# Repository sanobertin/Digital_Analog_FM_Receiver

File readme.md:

> [!CAUTION]
> This project is still in progress thus this repo will be changing often. 

## Project Description: 
_This project aims to design and implement a digital FM receiver capable of receiving analog FM radio signals and converting them into digital data. The project will include:_

### Hardware:

**Schematic and PCB Design:** A carefully designed schematic and PCB will be created to ensure optimal performance and reliability of the FM receiver circuit. </br>
**Arduino R4 Microcontroller**: This powerful 32-bit microcontroller will be used to process the digital output and interface with the PC. </br>
**Antenna:** An efficient antenna will be designed to capture FM signals effectively. </br>

### Software:
**Firmware:** The Arduino R4 will be programmed to:
- Receive FM signals from the antenna </br>
- Demodulate the signals to extract audio data </br>
- Convert the audio data into digital format </br>
- Transmit the digital data to the PC via a serial communication protocol </br>
- **PC Application:**
  - C++: Program the arduino microcontroller </br>
  - C#: A C# application will be created to provide a user-friendly interface for controlling the receiver and visualizing the received data. </br> 

**Key Features:**
- **High-Quality Audio Reception:** The receiver will be optimized for clear and accurate audio reproduction. </br>
- **Reliable Data Transmission:** The serial communication between the Arduino and PC will ensure robust data transfer. </br>
- **Flexible Software Interface:** The C++ and C# applications will offer versatility for different use cases. </br>
- **Customizable Hardware:** The modular design will allow for easy customization and experimentation. </br>

## Project Goals:
- Successfully design and build a functional FM receiver. </br>
- Demonstrate the ability to interface the receiver with a PC using a microcontroller. </br>
- Develop user-friendly software applications for data processing and visualization. </br>
- Explore potential applications for the receiver, such as audio streaming, signal analysis, and more. </br>
- By combining hardware and software expertise, this project aims to provide a comprehensive solution for digital FM reception and processing. </br>

## Tools used: 
- KiCAD </br>
- IDEs: </br>
- Google Gemini & GPT 4.xx </br>
- etc. </br>
## Resources: 
- FM Radio block diagrams: https://users.encs.concordia.ca/~paknys/block.pdf
- Antenna selection: https://www.ahsystems.com/articles/antenna-selection.php

### Board Schematic 

### PCB

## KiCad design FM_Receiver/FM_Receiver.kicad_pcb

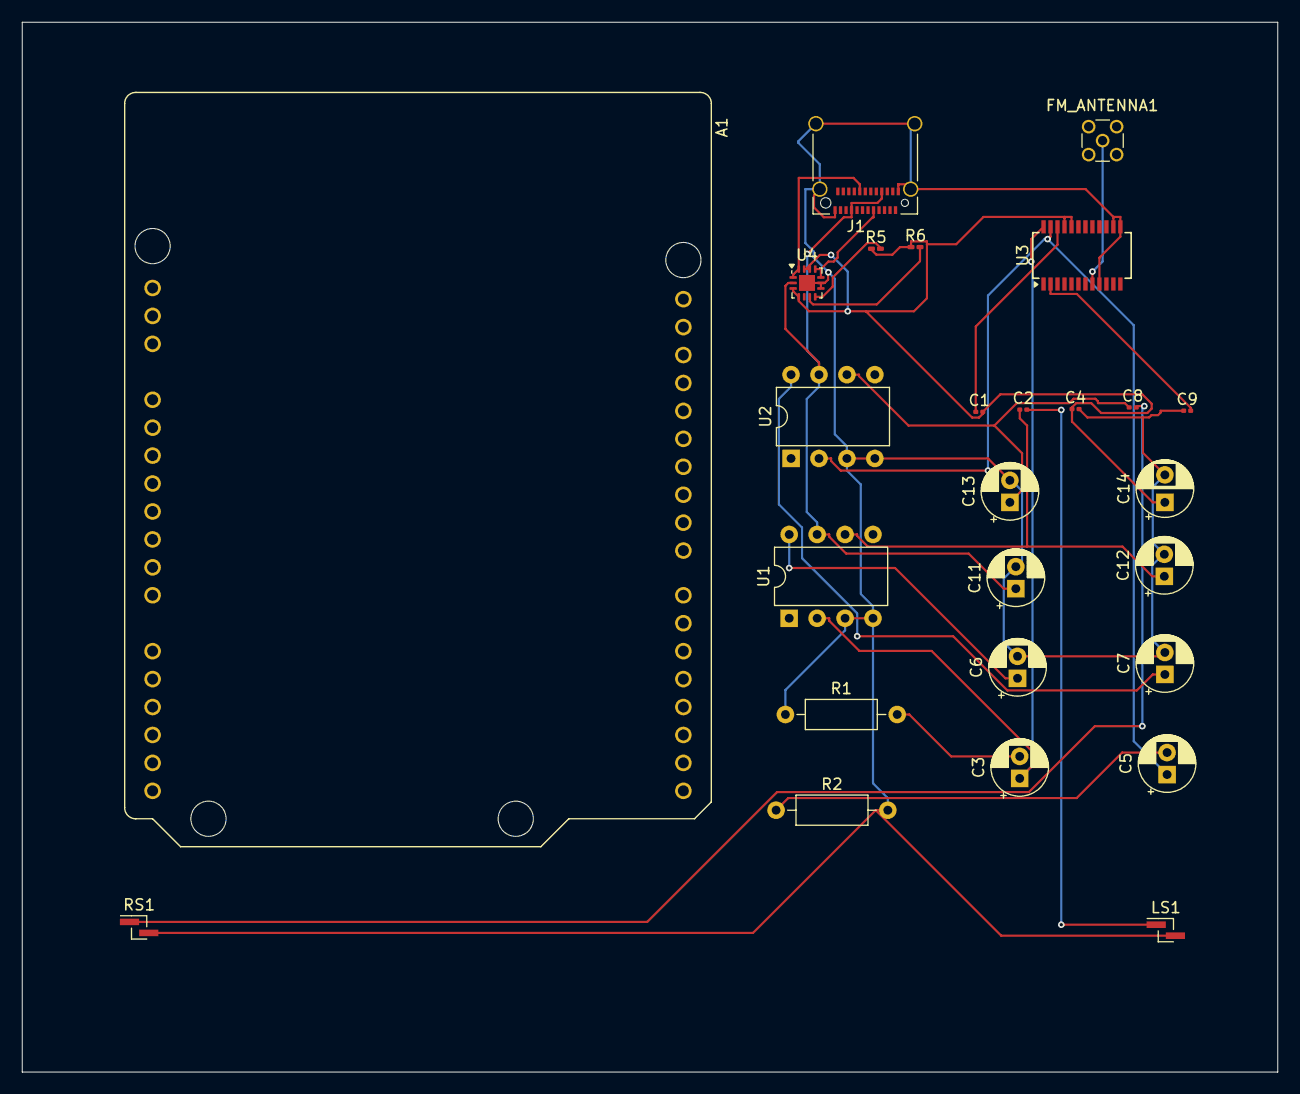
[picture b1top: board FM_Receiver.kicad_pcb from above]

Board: 2 copper layers, 114.2 x 95.5 mm, 26 parts (0 on the bottom side), 20 nets.

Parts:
A1: Arduino_Uno_R4_WiFi_Shield; ARDUINO UNO R4 WIFI_ABX00087
C1: 22nF; C_0201_0603Metric
C2, C8: 500µ; C_0201_0603Metric
C3, C5, C12, C13: 5uF_50V; CP_Radial_D5.0mm_P2.00mm
C4: 100nF; C_0201_0603Metric
C6, C7, C11: 500uF_50V; CP_Radial_D5.0mm_P2.00mm
C9: 4.5pF; C_0201_0603Metric
C14: 10µ; CP_Radial_D5.0mm_P2.50mm
FM_ANTENNA1: Antenna; MMCX_Molex_73415-1471_Vertical
J1: USB_C_Receptacle_PowerOnly_6P; USB_C_Receptacle_Amphenol_12401610E4-2A_CircularHoles
LS1: Speaker; PinHeader_1x02_P1.00mm_Vertical_SMD_Pin1Left
R1, R2: 10k; R_Axial_DIN0207_L6.3mm_D2.5mm_P10.16mm_Horizontal
R5, R6: 5K; R_0201_0603Metric_Pad0.64x0.40mm_HandSolder
RS1: Speaker; PinHeader_1x02_P1.00mm_Vertical_SMD_Pin1Left
U1, U2: LM380N-8; DIP-8_W7.62mm
U3: Si4731-D60-GU; SSOP-24_3.9x8.7mm_P0.635mm
U4: FUSB302B01MPX; WQFN-14-1EP_2.5x2.5mm_P0.5mm_EP1.45x1.45mm

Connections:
+3.3V: C1.2 (-), C4.1 (+), C14.1, R5.1 (+), R6.1 (+), U3.20 (VD), U3.21 (VA), U4.3 (VDD), U4.4 (VDD), U4.12 (VCONN), U4.13 (VCONN)
+12V: C11.1, J1.A9 (VBUS), J1.B9 (VBUS), U1.7 (VS), U2.7 (VS), U4.2 (VBUS)
DFS/2: C9.2 (-), U3.2 (DFS)
GND: C4.2 (-), C6.2, C7.2, C9.1 (+), C11.2, C12.2, C13.2, C14.2, J1.A12 (GND), J1.B12 (GND), J1.S1 (SHIELD), LS1.2, R1.1, R2.2, RS1.2, U1.3 (-), U1.4 (GND), U2.3 (-), U2.4 (GND), U3.9 (RFGND), U3.13 (GND), U3.14 (GND), U4.8 (GND), U4.9 (GND), U4.15 (GND)
LOUT/24: C3.1, U1.2 (+), U3.24 (LOUT/[DFS])
unnamed: C1.1 (+), U3.22 (DBYP)
unnamed: C2.1 (+), C12.1, U1.6
unnamed: C2.2 (-), LS1.1
unnamed: C3.2, R1.2
unnamed: C5.2, R2.1
unnamed: C8.1 (+), C13.1, U2.6
unnamed: C8.2 (-), RS1.1
unnamed: FM_ANTENNA1.1 (A), U3.8 (FMI)
unnamed: J1.A5 (CC1), U4.10 (CC1), U4.11 (CC1)
unnamed: J1.B5 (CC2), U4.1 (CC2), U4.14 (CC2)
unnamed: R5.2 (-), U4.7 (SDA)
unnamed: R6.2 (-), U4.6 (SCL)
unnamed: C6.1, U1.8 (BYPASS)
unnamed: C7.1, U2.8 (BYPASS)
ROUT/23: C5.1, U2.2 (+), U3.23 (ROUT/[DOUT])

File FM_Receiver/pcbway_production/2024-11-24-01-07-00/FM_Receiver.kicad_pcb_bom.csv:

Designator,Quantity,Value,Footprint,Package,MPN,DNP,Mount_Type,Description,Indicator,Rating
A1,1,Arduino_Uno_R4_WiFi_Shield,ARDUINO UNO R4 WIFI_ABX00087,,,,tht,Shield for Arduino Uno R4 WiFi,,
C1,1,22nF,C_0201_0603Metric,,,,smt,"capacitor, non-polarized/bipolar",+,V
"C11, C6, C7",3,500uF_50V,CP_Radial_D5.0mm_P2.00mm,,,,tht,"22uF, 50V Electrolytic Capacitor",,
"C12, C13, C3, C5",4,5uF_50V,CP_Radial_D5.0mm_P2.00mm,,,,tht,"22uF, 50V Electrolytic Capacitor",,
C14,1,10µ,CP_Radial_D5.0mm_P2.50mm,,,,tht,Polarized Capacitor,,
"C2, C8",2,500µ,C_0201_0603Metric,,,,smt,"capacitor, non-polarized/bipolar",+,V
C4,1,100nF,C_0201_0603Metric,,,,smt,"capacitor, non-polarized/bipolar",+,V
C9,1,4.5pF,C_0201_0603Metric,,,,smt,"capacitor, non-polarized/bipolar",+,V
FM_ANTENNA1,1,Antenna,MMCX_Molex_73415-1471_Vertical,,,,tht,Antenna,,
J1,1,USB_C_Receptacle_PowerOnly_6P,USB_C_Receptacle_Amphenol_12401610E4-2A_CircularHoles,,,,smt,USB Power-Only 6P Type-C Receptacle connector,,
"LS1, RS1",2,Speaker,PinHeader_1x02_P1.00mm_Vertical_SMD_Pin1Left,,,,smt,Speaker,,
"R1, R2",2,10k,R_Axial_DIN0207_L6.3mm_D2.5mm_P10.16mm_Horizontal,,,,tht,"10kΩ, 1/4W Resistor",,
"R5, R6",2,5K,R_0201_0603Metric_Pad0.64x0.40mm_HandSolder,,,,smt,resistor,+,W
"U1, U2",2,LM380N-8,DIP-8_W7.62mm,,,,tht,"2.5W Audio Power Amplifier, PDIP-8",,
U3,1,Si4731-D60-GU,SSOP-24_3.9x8.7mm_P0.635mm,,,,smt,AM/FM Broadcast Radio Receiver with RDS/RBDS,,
U4,1,FUSB302B01MPX,WQFN-14-1EP_2.5x2.5mm_P0.5mm_EP1.45x1.45mm,,,,smt,"Programmable USB Type-C Controller w/PD, I2C address 0x23, WQFN-14",,

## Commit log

2024-11-20 new repo
2024-11-28 Update readme.md ~ project description and purpose
2024-12-04 new updates
    Dec. 3 update
2024-12-04 gitignore update
